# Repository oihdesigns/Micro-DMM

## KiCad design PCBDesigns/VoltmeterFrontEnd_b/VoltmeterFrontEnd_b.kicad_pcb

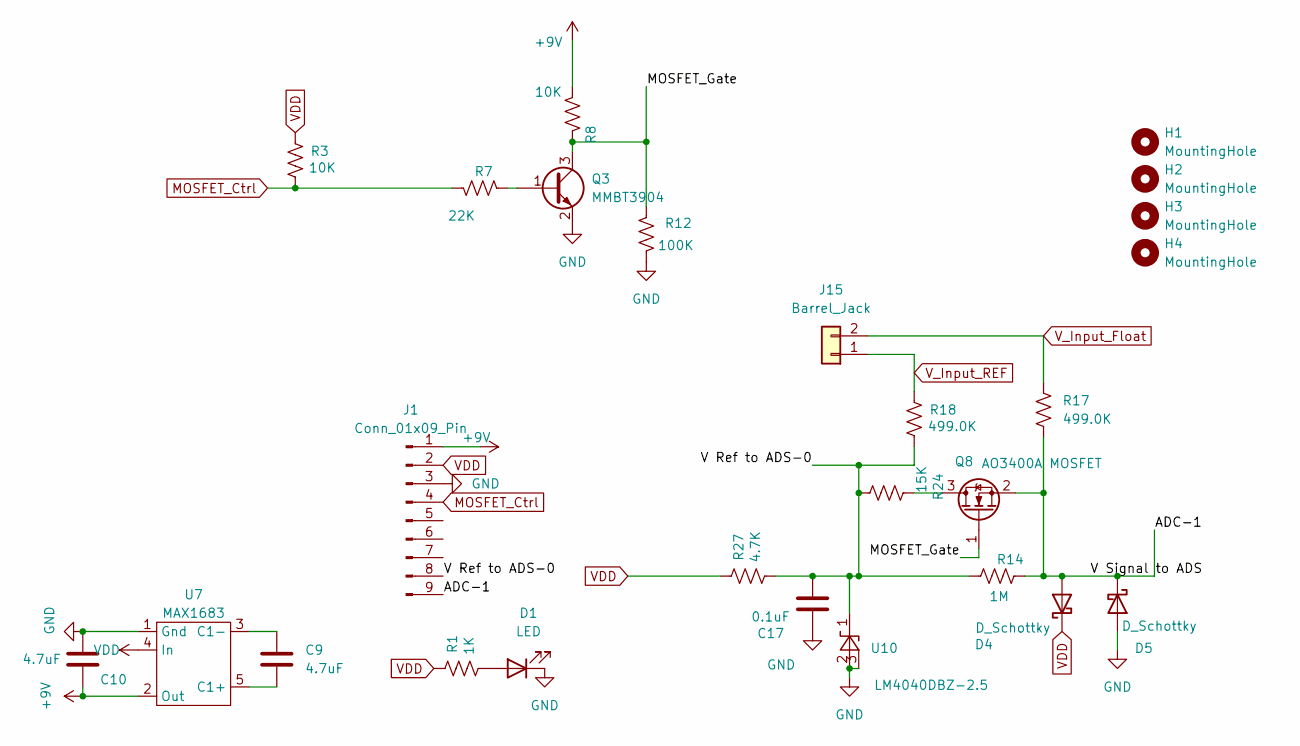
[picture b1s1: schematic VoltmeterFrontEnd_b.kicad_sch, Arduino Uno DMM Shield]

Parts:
C9, C10: 4.7uF; C_0805_2012Metric_Pad1.18x1.45mm_HandSolder
C17: 0.1uF; C_0805_2012Metric_Pad1.18x1.45mm_HandSolder
D1: LED; LED_0805_2012Metric_Pad1.15x1.40mm_HandSolder
D4, D5: D_Schottky; D_SOD-123
H1, H2, H3, H4: MountingHole; MountingHole_3.2mm_M3_DIN965_Pad_TopBottom
J1: Conn_01x09_Pin; PinHeader_1x09_P2.54mm_Vertical
J15: Barrel_Jack; TerminalBlock_Phoenix_MKDS-3-2-5.08_1x02_P5.08mm_Horizontal
Q3: MMBT3904; SOT-23
Q8: AO3400A MOSFET; SOT-23
R1: 1K; R_0805_2012Metric_Pad1.20x1.40mm_HandSolder
R3, R8: 10K; R_0805_2012Metric_Pad1.20x1.40mm_HandSolder
R7: 22K; R_0805_2012Metric_Pad1.20x1.40mm_HandSolder
R12: 100K; R_0805_2012Metric_Pad1.20x1.40mm_HandSolder
R14: 1M; R_0805_2012Metric_Pad1.20x1.40mm_HandSolder
R17, R18: 499.0K; R_0805_2012Metric_Pad1.20x1.40mm_HandSolder
R24: 15K; R_0805_2012Metric_Pad1.20x1.40mm_HandSolder
R27: 4.7K; R_0805_2012Metric_Pad1.20x1.40mm_HandSolder
U7: MAX1683; SOT-23-5_HandSoldering
U10: LM4040DBZ-2.5; SOT-23

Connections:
+9V: C10.2, J1.1, R8.2, U7.2 (Out)
/ADC-1: D4.2 (A), D5.1 (K), J1.9, Q8.2 (S), R14.2, R17.2
/MOSFET_Gate: Q3.3 (C), Q8.1 (G), R8.1, R12.2
/V Ref to ADS-0: C17.2, J1.8, R14.1, R18.2, R24.2, R27.2, U10.1 (K)
GND: C10.1, C17.1, D1.1 (K), D5.2 (A), J1.3, Q3.2 (E), R12.1, U7.1 (Gnd), U10.2 (A), U10.3 (nc_(gnd))
MOSFET_Ctrl: J1.4, R3.2, R7.1
unnamed: D1.2 (A), R1.2
unnamed: Q3.1 (B), R7.2
unnamed: Q8.3 (D), R24.1
unnamed: C9.2, U7.5 (C1+)
unnamed: C9.1, U7.3 (C1-)
VDD: D4.1 (K), J1.2, R1.1, R3.1, R27.1, U7.4 (In)
V_Input_Float: J15.2, R17.1
V_Input_REF: J15.1, R18.1

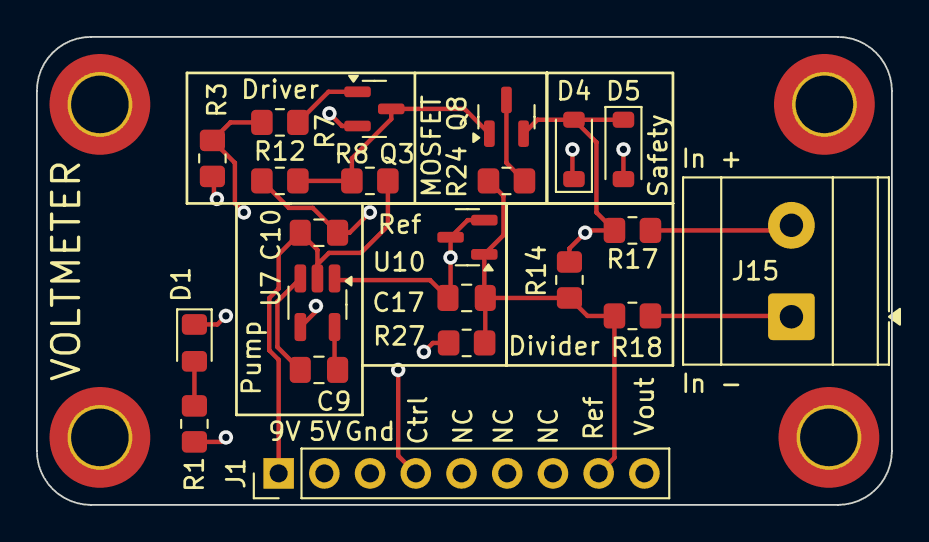
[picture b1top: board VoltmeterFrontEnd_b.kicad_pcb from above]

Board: 4 copper layers, 47.5 x 26.0 mm, 26 parts (0 on the bottom side), 14 nets.

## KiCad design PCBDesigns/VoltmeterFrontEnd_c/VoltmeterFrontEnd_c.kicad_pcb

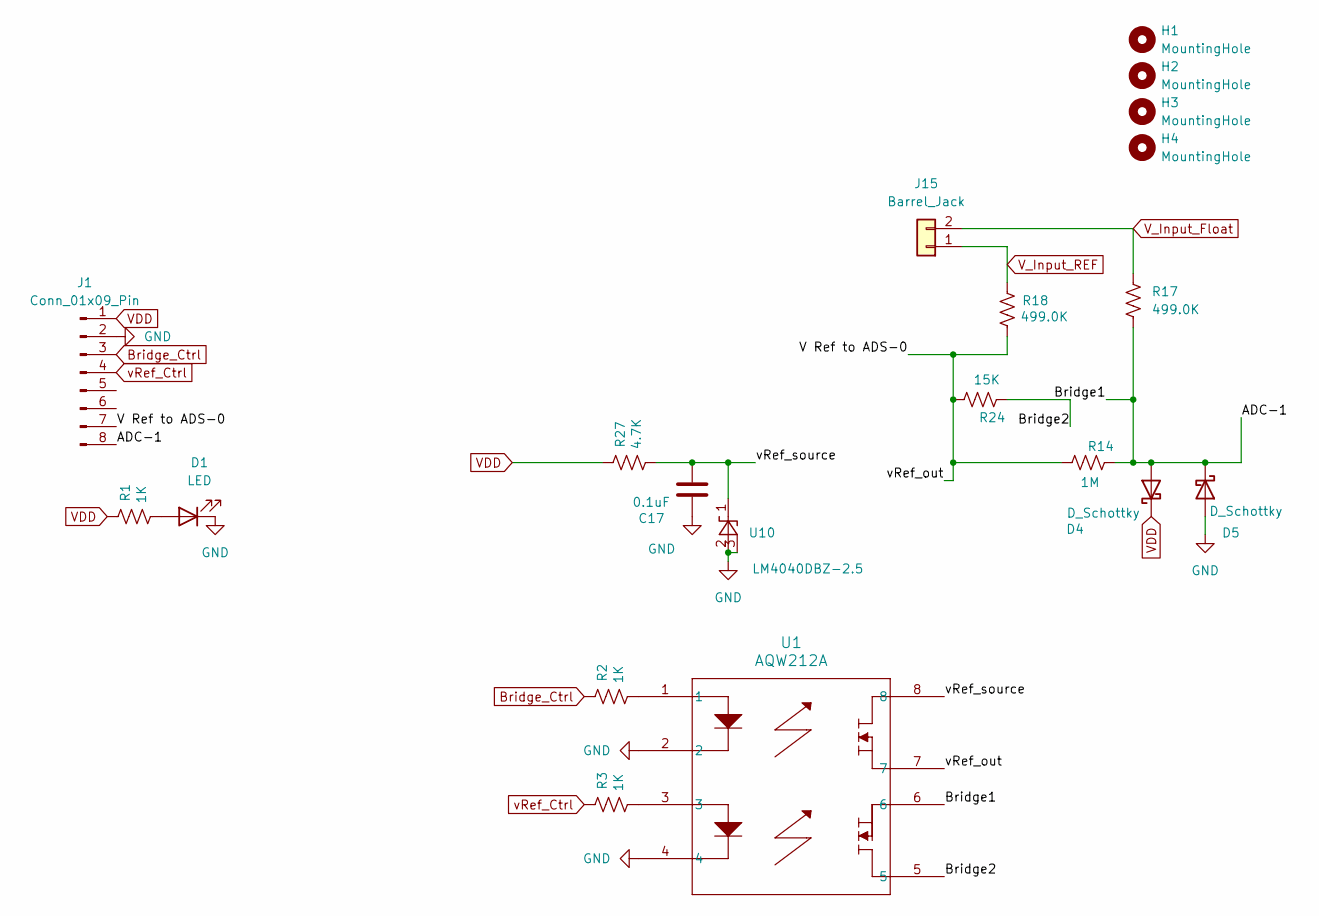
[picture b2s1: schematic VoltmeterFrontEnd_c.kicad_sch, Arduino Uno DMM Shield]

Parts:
C17: 0.1uF; C_0805_2012Metric_Pad1.18x1.45mm_HandSolder
D1: LED; LED_0805_2012Metric_Pad1.15x1.40mm_HandSolder
D4, D5: D_Schottky; D_SOD-123
H1, H2, H3, H4: MountingHole; MountingHole_3.2mm_M3_DIN965_Pad_TopBottom
J1: Conn_01x09_Pin; PinHeader_1x08_P2.54mm_Vertical
J15: Barrel_Jack; TerminalBlock_Phoenix_MKDS-3-2-5.08_1x02_P5.08mm_Horizontal
R1, R2, R3: 1K; R_0805_2012Metric_Pad1.20x1.40mm_HandSolder
R14: 1M; R_0805_2012Metric_Pad1.20x1.40mm_HandSolder
R17, R18: 499.0K; R_0805_2012Metric_Pad1.20x1.40mm_HandSolder
R24: 15K; R_0805_2012Metric_Pad1.20x1.40mm_HandSolder
R27: 4.7K; R_0805_2012Metric_Pad1.20x1.40mm_HandSolder
U1: AQW212A; SOP-8_6.605x9.655mm_P2.54mm
U10: LM4040DBZ-2.5; SOT-23

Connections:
/ADC-1: D4.2 (A), D5.1 (K), J1.8, R14.2, R17.2, U1.6
/Bridge2: R24.1, U1.5
/V Ref to ADS-0: J1.7, R14.1, R18.2, R24.2, U1.7
/vRef_source: C17.2, R27.2, U1.8, U10.1 (K)
Bridge_Ctrl: J1.3, R2.1
GND: C17.1, D1.1 (K), D5.2 (A), J1.2, U1.2, U1.4, U10.2 (A), U10.3 (nc_(gnd))
unnamed: D1.2 (A), R1.2
unnamed: R2.2, U1.1
unnamed: R3.2, U1.3
VDD: D4.1 (K), J1.1, R1.1, R27.1
V_Input_Float: J15.2, R17.1
V_Input_REF: J15.1, R18.1
vRef_Ctrl: J1.4, R3.1

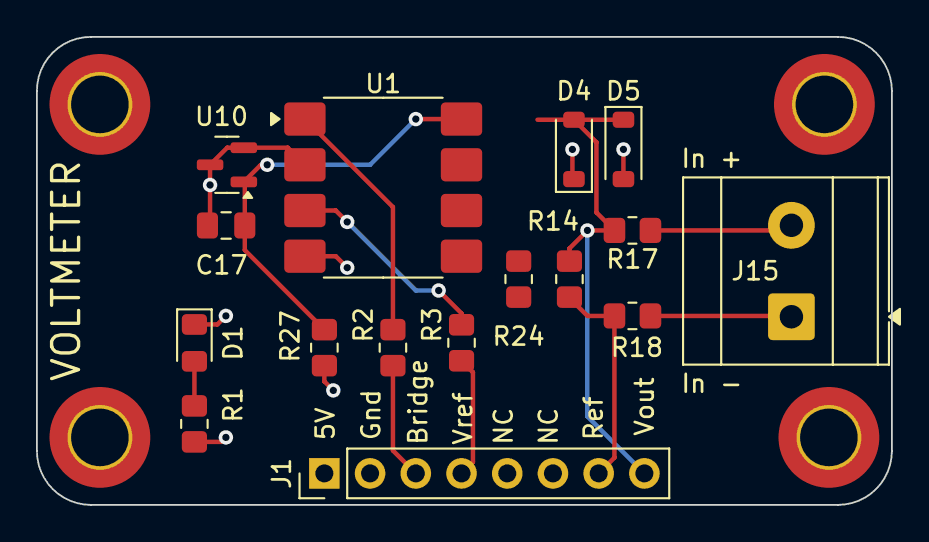
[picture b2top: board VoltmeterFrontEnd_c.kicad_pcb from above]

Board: 4 copper layers, 47.5 x 26.0 mm, 20 parts (0 on the bottom side), 13 nets.
